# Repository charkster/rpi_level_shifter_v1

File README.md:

# rpi_level_shifter_v1
Raspberry Pi level shifter for 10 signals (two boards can fit on the same 40 pin header). Two NVT2010PW ICs are available on a single board, to either level shift from 3.3V to 5V or from 3.3V to 1.8V and 1.2V (jumper selectable). The RPi's 5V is used for the 5V level shift and two on-board LDO regulators are available for shifting levels down to 1.8V or 1.2V. Other voltages can be used, but it is recommended that they not be between 2.6V and 4.3V.  

This board is designed to not fit over-top the RPi board, but rather over the side.

Each board needs to have the top-left pin of J1 connected to the 3.3V RPi header pin. One board can service the I2C and UART pins (along with a couple of GPIO) and another board can service SPI pins. BCM GPIO's 13, 16, 19, 20, 21 and 26 are not accessable with this board.

Check-out my **PDF** [schematic](https://github.com/charkster/rpi_level_shifter_v1/blob/main/rpi_8x2_v1.pdf) !!

Check-out the CSV [**Bill of Materials**](https://github.com/charkster/rpi_level_shifter_v1/blob/main/rpi_8x2_v1_BOM.csv) !!

**The J3 connector must only have one horizontal jumper!! Either HV_EN or LV_EN, or damage to the RPi pins may occur (you have been warned). Additionally, the J4 connector must only have one horizontal jumper!! The RPI_5V is only available if the level shifter board is at the top of the header, otherwise you will need to jumper wire the 5V to the VEXT pin.**

**UPDATES:**
SPI at 5V is working well to 10MHz with the 1k Ohm pull-up resistors. This matches nicely with the NVT2010PW datasheet. I lowered the pull-up resistors to 500 Ohm and was able to get SPI working at 12MHz. I was not able to run faster than 12MHz at 5V. Power consumption was about 0.5W for both the 0.5k and 1k pull-up resistors.

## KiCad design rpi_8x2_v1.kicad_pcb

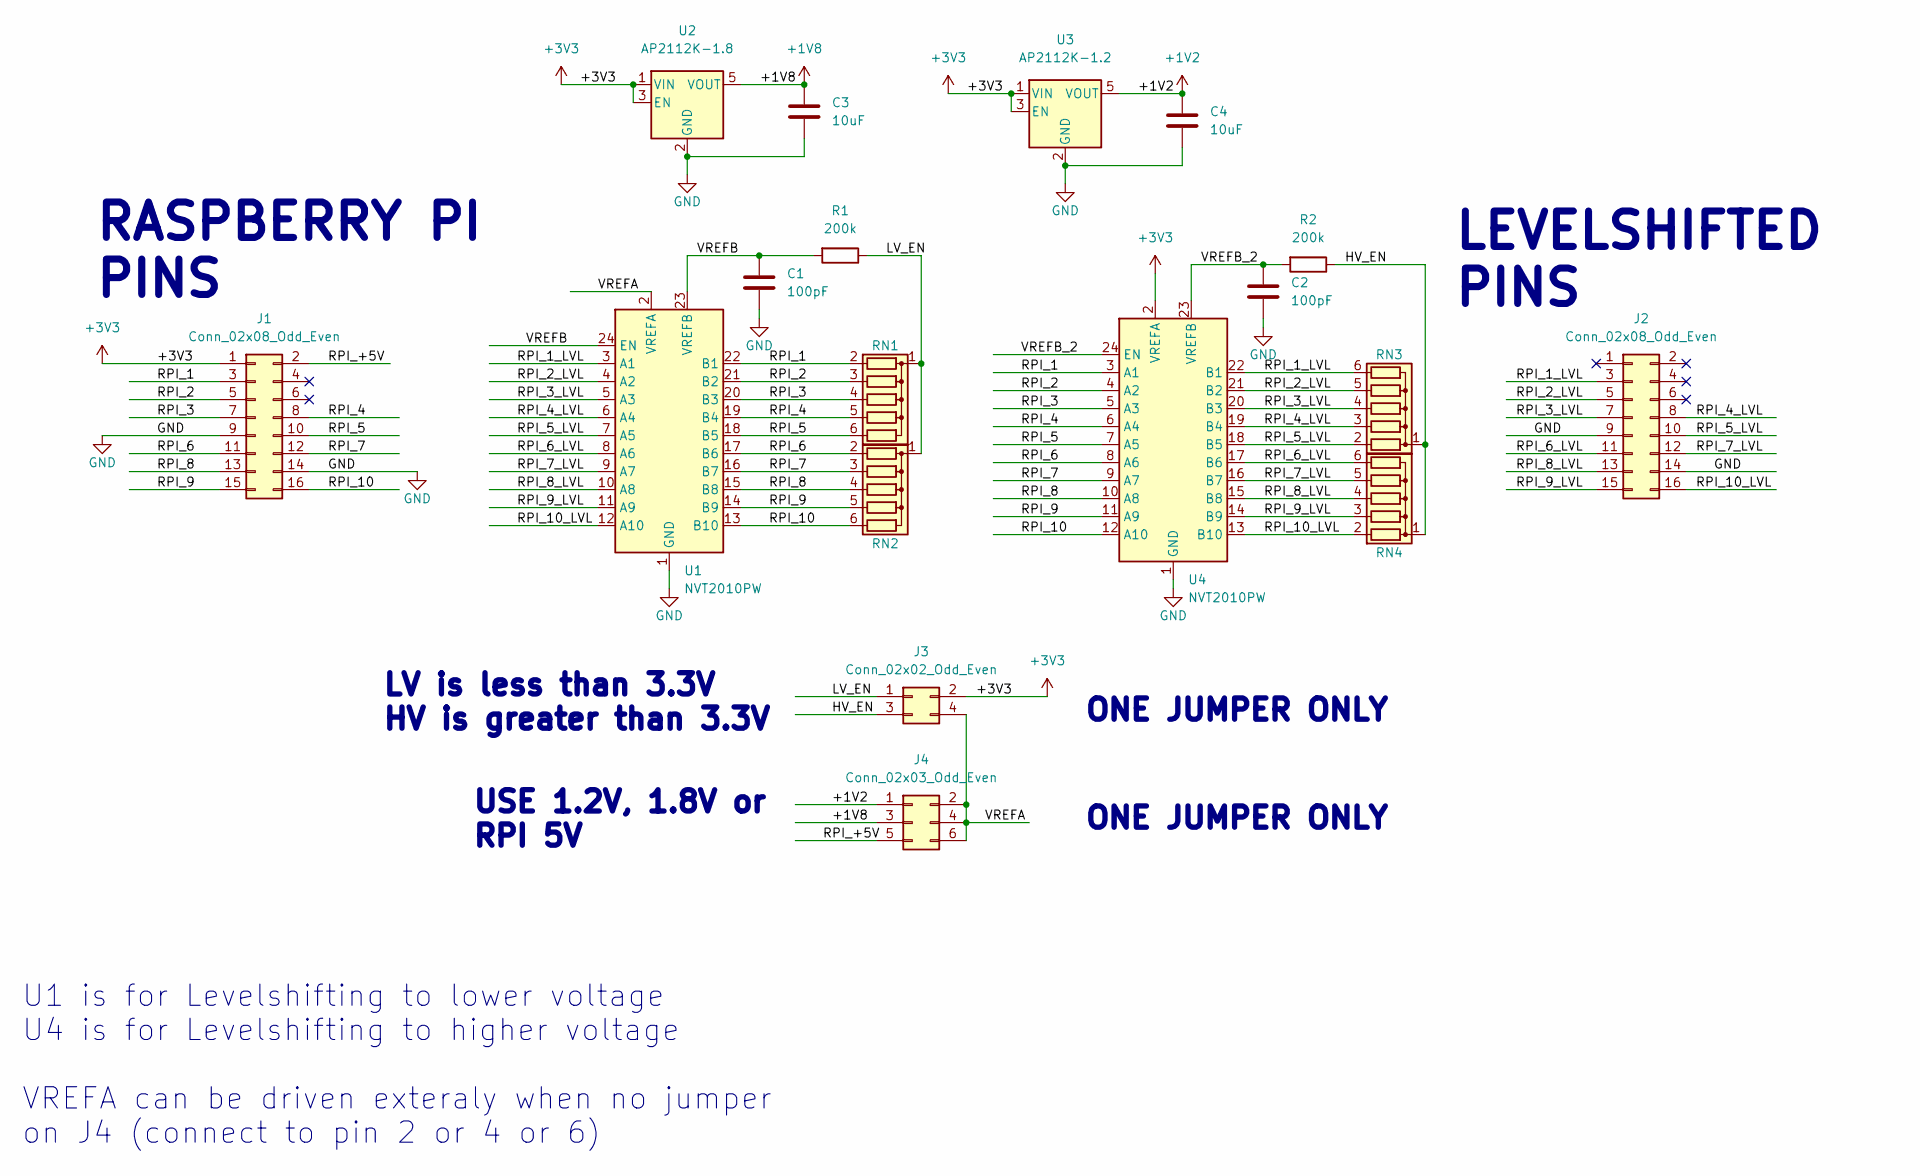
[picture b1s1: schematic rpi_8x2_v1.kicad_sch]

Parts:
C1, C2: 100pF; R_0603_1608Metric
C3, C4: 10uF; R_0603_1608Metric
J1, J2: Conn_02x08_Odd_Even; PinHeader_2x08_P2.54mm_Vertical
J3: Conn_02x02_Odd_Even; PinHeader_2x02_P2.54mm_Vertical
J4: Conn_02x03_Odd_Even; PinHeader_2x03_P2.54mm_Vertical
R1, R2: 200k; C_0603_1608Metric
RN1, RN2, RN3, RN4: R_Network05; R_Array_SIP6
U1, U4: NVT2010PW; TSSOP-24_4.4x7.8mm_P0.65mm
U2: AP2112K-1.8; SOT-23-5
U3: AP2112K-1.2; SOT-23-5

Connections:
+1V2: C4.1, J4.1, U3.5 (VOUT)
+1V8: C3.1, J4.3, U2.5 (VOUT)
+3V3: J1.1, J3.2, U2.1 (VIN), U2.3 (EN), U3.1 (VIN), U3.3 (EN), U4.2 (VREFA)
/HV_EN: J3.3, R2.1, RN3.1 (common), RN4.1 (common)
/LV_EN: J3.1, R1.1, RN1.1 (common), RN2.1 (common)
/RPI_1: J1.3, RN1.2 (R1), U1.22 (B1), U4.3 (A1)
/RPI_1_LVL: J2.3, RN3.6 (R5), U1.3 (A1), U4.22 (B1)
/RPI_2: J1.5, RN1.3 (R2), U1.21 (B2), U4.4 (A2)
/RPI_2_LVL: J2.5, RN3.5 (R4), U1.4 (A2), U4.21 (B2)
/RPI_3: J1.7, RN1.4 (R3), U1.20 (B3), U4.5 (A3)
/RPI_3_LVL: J2.7, RN3.4 (R3), U1.5 (A3), U4.20 (B3)
/RPI_4: J1.8, RN1.5 (R4), U1.19 (B4), U4.6 (A4)
/RPI_4_LVL: J2.8, RN3.3 (R2), U1.6 (A4), U4.19 (B4)
/RPI_5: J1.10, RN1.6 (R5), U1.18 (B5), U4.7 (A5)
/RPI_5_LVL: J2.10, RN3.2 (R1), U1.7 (A5), U4.18 (B5)
/RPI_6: J1.11, RN2.2 (R1), U1.17 (B6), U4.8 (A6)
/RPI_6_LVL: J2.11, RN4.6 (R5), U1.8 (A6), U4.17 (B6)
/RPI_7: J1.12, RN2.3 (R2), U1.16 (B7), U4.9 (A7)
/RPI_7_LVL: J2.12, RN4.5 (R4), U1.9 (A7), U4.16 (B7)
/RPI_8: J1.13, RN2.4 (R3), U1.15 (B8), U4.10 (A8)
/RPI_8_LVL: J2.13, RN4.4 (R3), U1.10 (A8), U4.15 (B8)
/RPI_9: J1.15, RN2.5 (R4), U1.14 (B9), U4.11 (A9)
/RPI_9_LVL: J2.15, RN4.3 (R2), U1.11 (A9), U4.14 (B9)
/RPI_10: J1.16, RN2.6 (R5), U1.13 (B10), U4.12 (A10)
/RPI_10_LVL: J2.16, RN4.2 (R1), U1.12 (A10), U4.13 (B10)
/RPI_+5V: J1.2, J4.5
/VREFA: J3.4, J4.2, J4.4, J4.6, U1.2 (VREFA)
/VREFB: C1.1, R1.2, U1.23 (VREFB), U1.24 (EN)
/VREFB_2: C2.1, R2.2, U4.23 (VREFB), U4.24 (EN)
GND: C1.2, C2.2, C3.2, C4.2, J1.9, J1.14, J2.9, J2.14, U1.1 (GND), U2.2 (GND), U3.2 (GND), U4.1 (GND)

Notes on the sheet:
LEVELSHIFTED PINS
ONE JUMPER ONLY
RASPBERRY PI PINS
LV is less than 3.3V HV is greater than 3.3V
U1 is for Levelshifting to lower voltage U4 is for Levelshifting to higher voltage VREFA can be driven exteraly when no jumper on J4 (connect to pin 2 or 4 or 6)
USE 1.2V, 1.8V or RPI 5V

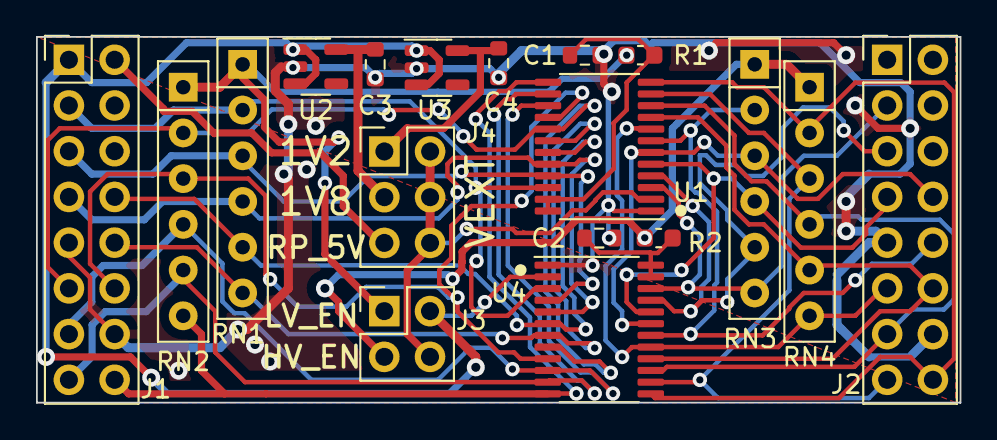
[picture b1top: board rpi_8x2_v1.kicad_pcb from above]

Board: 2 copper layers, 51.3 x 20.3 mm, 18 parts (0 on the bottom side), 30 nets.

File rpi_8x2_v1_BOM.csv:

Source:,rpi_8x2_v1.kicad_sch,,,,,
Date:,Wed 19 Apr 2023 10:41:58 PM MST,,,,,
Tool:,Eeschema 6.0.2+dfsg-1,,,,,
Generator:,/usr/share/kicad/plugins/bom_csv_grouped_by_value.py,,,,,
Component Count:,18,,,,,
,,,,,,
Individual Components:,,,,,,
,,,,,,
Item,Qty,Reference(s),Value,LibPart,Footprint,Datasheet
,,C1,100pF,Device:C,Resistor_SMD:R_0603_1608Metric,~
,,C2,100pF,Device:C,Resistor_SMD:R_0603_1608Metric,~
,,C3,10uF,Device:C,Resistor_SMD:R_0603_1608Metric,~
,,C4,10uF,Device:C,Resistor_SMD:R_0603_1608Metric,~
,,J1,Conn_02x08_Odd_Even,Connector_Generic:Conn_02x08_Odd_Even,Connector_PinHeader_2.54mm:PinHeader_2x08_P2.54mm_Vertical,~
,,J2,Conn_02x08_Odd_Even,Connector_Generic:Conn_02x08_Odd_Even,Connector_PinHeader_2.54mm:PinHeader_2x08_P2.54mm_Vertical,~
,,J3,Conn_02x02_Odd_Even,Connector_Generic:Conn_02x02_Odd_Even,Connector_PinHeader_2.54mm:PinHeader_2x02_P2.54mm_Vertical,~
,,J4,Conn_02x03_Odd_Even,Connector_Generic:Conn_02x03_Odd_Even,Connector_PinHeader_2.54mm:PinHeader_2x03_P2.54mm_Vertical,~
,,R1,200k,Device:R,Capacitor_SMD:C_0603_1608Metric,~
,,R2,200k,Device:R,Capacitor_SMD:C_0603_1608Metric,~
,,RN1,4606X-101-102LF,Device:R_Network05,Resistor_THT:R_Array_SIP6,https://www.mouser.com/datasheet/2/54/4600x-776645.pdf
,,RN2,4606X-101-102LF,Device:R_Network05,Resistor_THT:R_Array_SIP6,https://www.mouser.com/datasheet/2/54/4600x-776645.pdf
,,RN3,4606X-101-102LF,Device:R_Network05,Resistor_THT:R_Array_SIP6,https://www.mouser.com/datasheet/2/54/4600x-776645.pdf
,,RN4,4606X-101-102LF,Device:R_Network05,Resistor_THT:R_Array_SIP6,https://www.mouser.com/datasheet/2/54/4600x-776645.pdf
,,U1,NVT2010PW,rpi_8x2_v1:NVT2010PW,Package_SO:TSSOP-24_4.4x7.8mm_P0.65mm,https://www.nxp.com/docs/en/data-sheet/NVT2008_NVT2010.pdf
,,U2,AP2112K-1.8,Regulator_Linear:AP2112K-1.8,Package_TO_SOT_SMD:SOT-23-5,https://www.diodes.com/assets/Datasheets/AP2112.pdf
,,U3,AP2112K-1.2,Regulator_Linear:AP2112K-1.2,Package_TO_SOT_SMD:SOT-23-5,https://www.diodes.com/assets/Datasheets/AP2112.pdf
,,U4,NVT2010PW,rpi_8x2_v1:NVT2010PW,Package_SO:TSSOP-24_4.4x7.8mm_P0.65mm,https://www.nxp.com/docs/en/data-sheet/NVT2008_NVT2010.pdf
,,,,,,
,,,,,,
,,,,,,
Collated Components:,,,,,,
,,,,,,
Item,Qty,Reference(s),Value,LibPart,Footprint,Datasheet
1,2,"C1, C2",100pF,Device:C,Resistor_SMD:R_0603_1608Metric,~
2,2,"C3, C4",10uF,Device:C,Resistor_SMD:R_0603_1608Metric,~
3,2,"J1, J2",Conn_02x08_Odd_Even,Connector_Generic:Conn_02x08_Odd_Even,Connector_PinHeader_2.54mm:PinHeader_2x08_P2.54mm_Vertical,~
4,1,J3,Conn_02x02_Odd_Even,Connector_Generic:Conn_02x02_Odd_Even,Connector_PinHeader_2.54mm:PinHeader_2x02_P2.54mm_Vertical,~
5,1,J4,Conn_02x03_Odd_Even,Connector_Generic:Conn_02x03_Odd_Even,Connector_PinHeader_2.54mm:PinHeader_2x03_P2.54mm_Vertical,~
6,2,"R1, R2",200k,Device:R,Capacitor_SMD:C_0603_1608Metric,~
7,4,"RN1, RN2, RN3, RN4",4606X-101-102LF,Device:R_Network05,Resistor_THT:R_Array_SIP6,https://www.mouser.com/datasheet/2/54/4600x-776645.pdf
8,2,"U1, U4",NVT2010PW,rpi_8x2_v1:NVT2010PW,Package_SO:TSSOP-24_4.4x7.8mm_P0.65mm,https://www.nxp.com/docs/en/data-sheet/NVT2008_NVT2010.pdf
9,1,U2,AP2112K-1.8,Regulator_Linear:AP2112K-1.8,Package_TO_SOT_SMD:SOT-23-5,https://www.diodes.com/assets/Datasheets/AP2112.pdf
10,1,U3,AP2112K-1.2,Regulator_Linear:AP2112K-1.2,Package_TO_SOT_SMD:SOT-23-5,https://www.diodes.com/assets/Datasheets/AP2112.pdf

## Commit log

2023-04-20 Add files via upload
    Additional notes
2023-04-20 Update README.md
    Added BOM link
2023-04-20 Create LICENSE
